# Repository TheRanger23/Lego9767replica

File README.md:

Bill Of Materials:

C1: 10uF
C2: 100nF
T1: BC557B
R1: 2.2K Ohm

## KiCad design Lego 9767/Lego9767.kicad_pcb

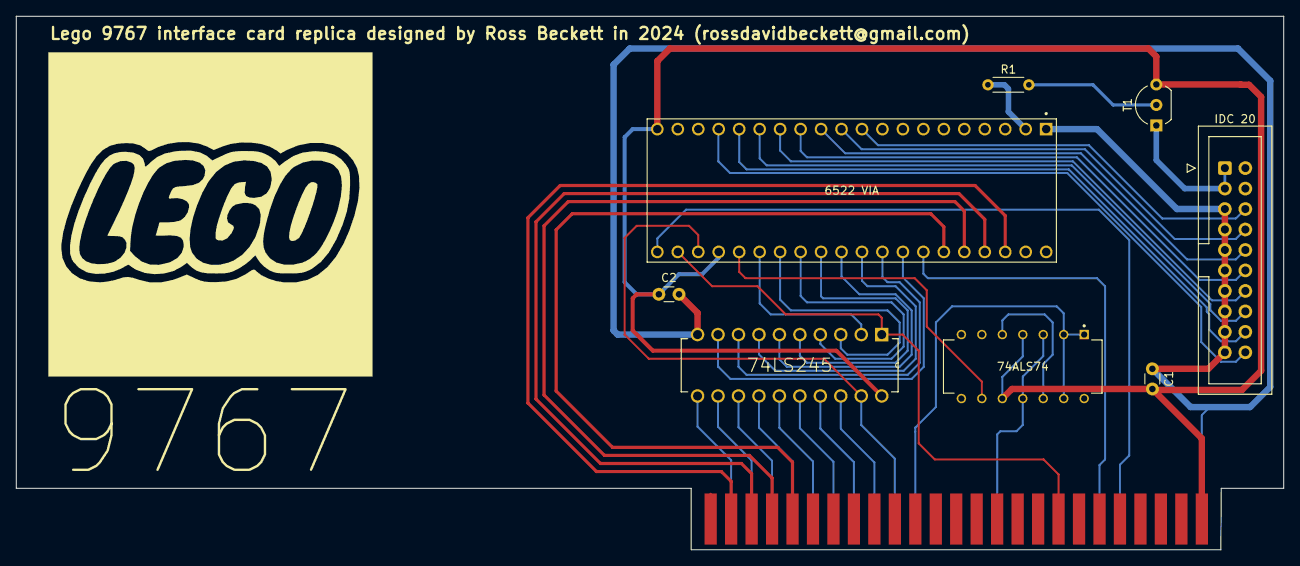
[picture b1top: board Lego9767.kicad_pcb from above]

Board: 2 copper layers, 157.3 x 66.2 mm, 9 parts (0 on the bottom side), 29 nets.

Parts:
74ALS74: DIP794W45P254L1969H508Q14
74LS245: DIP254P762X508-20
6522 VIA: AMPHENOL_DILB40P-223TLF
C1, C2: C1; C_Disc_D3.0mm_W1.6mm_P2.50mm
IDC 20: IDC-Header_2x10_P2.54mm_Vertical
J1: CARD EDGE; AppleIIBus
R1: R_Axial_DIN0204_L3.6mm_D1.6mm_P5.08mm_Horizontal
T1: TO-92_Inline_Wide_CEB

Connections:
+5V: 74ALS74.10, 74LS245.20, 6522 VIA.+5V, 6522 VIA.CS1, C1.2, C2.1, J1.25, T1.3
/7M: 74ALS74.3, 74ALS74.11, J1.36
/A0: 6522 VIA.38, J1.2
/A1: 6522 VIA.37, J1.3
/A2: 6522 VIA.36, J1.4
/A3: 6522 VIA.35, J1.5
/D0: 74LS245.11, J1.49
/D1: 74LS245.12, J1.48
/D2: 74LS245.13, J1.47
/D3: 74LS245.14, J1.46
/D4: 74LS245.15, J1.45
/D5: 74LS245.16, J1.44
/D6: 74LS245.17, J1.43
/D7: 74LS245.18, J1.42
/PHI0: 74ALS74.2, J1.40
/R~W: 74LS245.1, 6522 VIA.22, J1.18
/~DEVSEL: 74LS245.19, 6522 VIA.23, J1.41
/~IRQ: 6522 VIA.21, J1.30
/~RES: 6522 VIA.34, J1.31
GND: 74LS245.10, 6522 VIA.VSS, C1.1, C2.2, IDC 20.5, IDC 20.7, IDC 20.9, IDC 20.11, IDC 20.13, IDC 20.15, IDC 20.17, IDC 20.19, J1.26
PA0: 6522 VIA.PA0, R1.1, R1.2, T1.2
PB0: 6522 VIA.PB0, IDC 20.6
PB1: 6522 VIA.PB1, IDC 20.8
PB2: 6522 VIA.PB2, IDC 20.10
PB3: 6522 VIA.PB3, IDC 20.12
PB4: 6522 VIA.PB4, IDC 20.14
PB5: 6522 VIA.PB5, IDC 20.16
PB6: 6522 VIA.PB6, IDC 20.18
PB7: 6522 VIA.PB7, IDC 20.20
